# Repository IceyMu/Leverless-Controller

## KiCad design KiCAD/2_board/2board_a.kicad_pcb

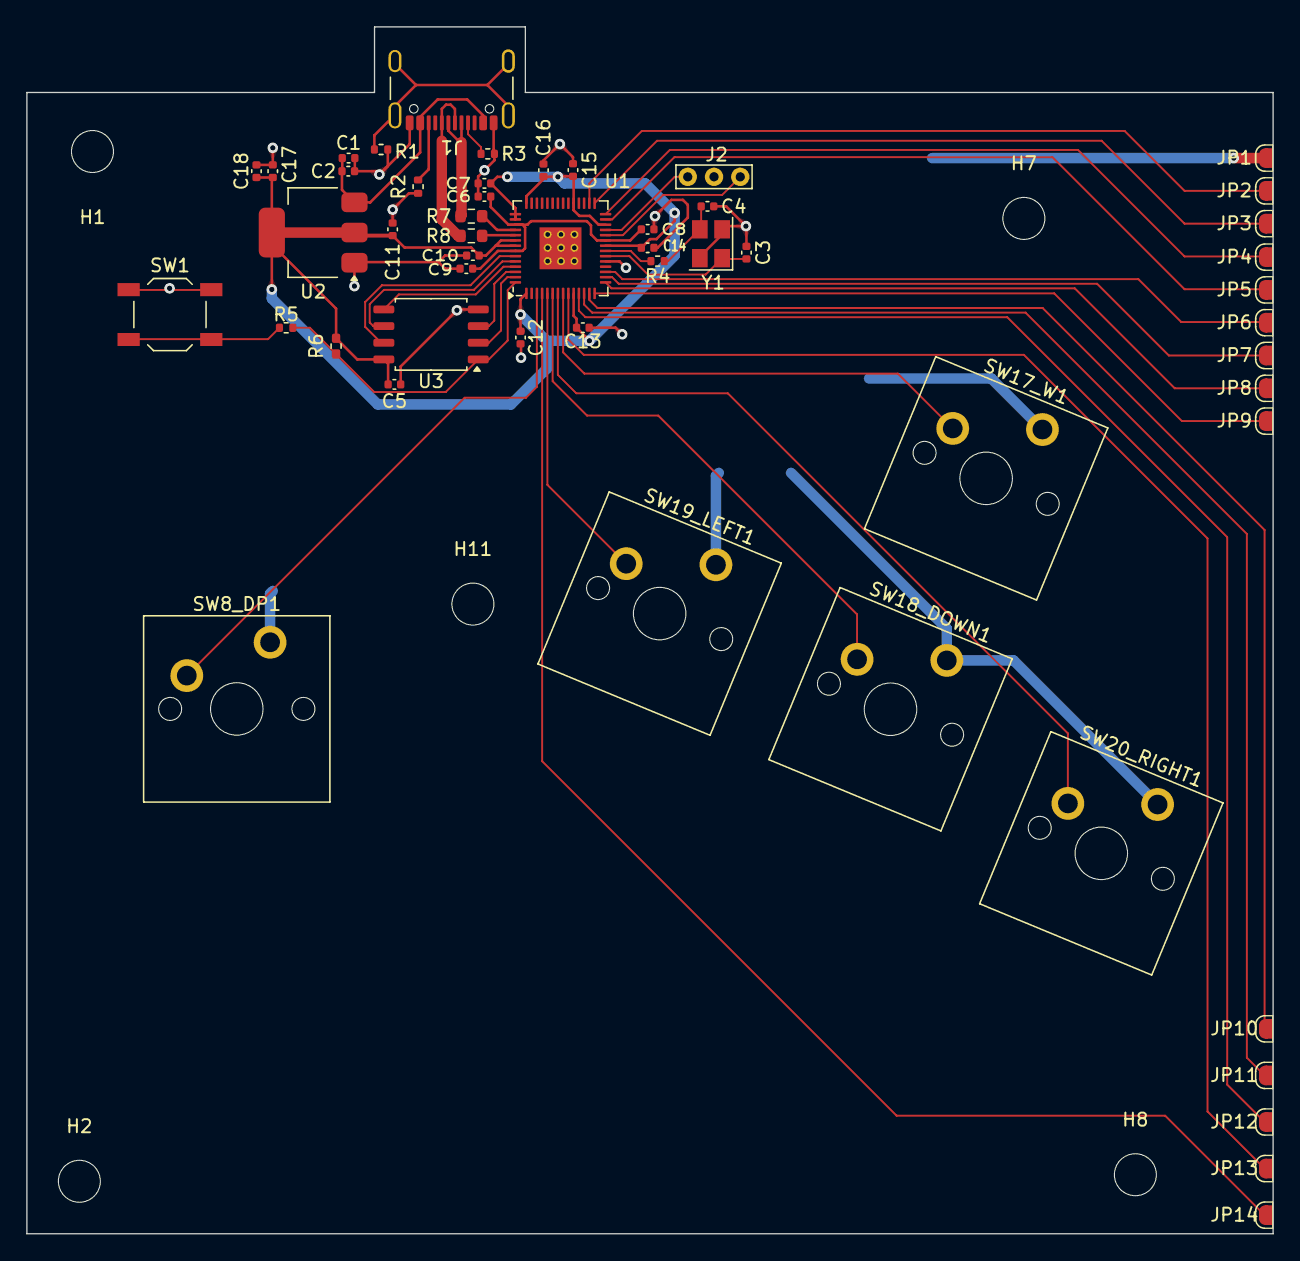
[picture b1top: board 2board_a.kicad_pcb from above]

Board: 2 copper layers, 95.0 x 92.0 mm, 58 parts (0 on the bottom side), 41 nets.

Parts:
B1: Board
C1, C2, C17, C18: 4.7u; C_0402_1005Metric
C3, C4: 15p; C_0402_1005Metric
C5, C8, C9, C10, C11, C12, C13, C14, C15, C16: 100n; C_0402_1005Metric
C6, C7: 1u; C_0402_1005Metric
H1, H2, H7, H8, H11: MountingHole; MountingHole_3.2mm_M3
J1: USB_C_Receptacle_USB2.0_14P; USB_C_Receptacle_U262-161N-4BVC11
J2: Conn_01x03_Socket; Debug_Points
JP1, JP2, JP3, JP4, JP5, JP6, JP7, JP8, JP9, JP10, JP11, JP12, JP13, JP14: SolderJumper_2_Bridged; EdgeSolderJumper-2_Left_Half
R1: 1M; R_0402_1005Metric
R2, R3: 5.1K; R_0402_1005Metric
R4, R5: 1K; R_0402_1005Metric
R6: DNF; R_0402_1005Metric_Pad0.72x0.64mm_HandSolder
R7, R8: 27; R_0603_1608Metric
SW1: Memory Reset; SW_SPST_TL3342
SW8_DP1: SW_Push; SW_Cherry_MX_PCB
SW17_W1, SW18_DOWN1, SW19_LEFT1, SW20_RIGHT1: SW_Push; SW_Cherry_MX_PCB_1.00u
U1: RP2040; QFN-56-1EP_7x7mm_P0.4mm_EP3.2x3.2mm
U2: AMS1117-3.3_SOT223; SOT-223-3_TabPin2
U3: W25Q128JVSIQ; SOIC-8_5.23x5.23mm_P1.27mm
Y1: 12 mhz crystal; Crystal_SMD_3225-4Pin_3.2x2.5mm

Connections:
+1V1: C6.1, C8.1, C9.1, U1.23 (DVDD), U1.45 (VREG_VOUT), U1.50 (DVDD)
+3.3V: C5.1, C7.1, C10.1, C11.1, C12.1, C13.1, C14.1, C15.1, C16.1, C17.1, C18.1, R6.1, U1.1 (IOVDD), U1.10 (IOVDD), U1.22 (IOVDD), U1.26 (RUN), U1.33 (IOVDD), U1.42 (IOVDD), U1.43 (ADC_AVDD), U1.44 (VREG_IN), U1.48 (USB_VDD), U1.49 (IOVDD), U2.2 (VO), U3.8 (VCC)
/Main/A1: JP4.1 (A), U1.28 (GPIO17)
/Main/A2: JP5.1 (A), U1.27 (GPIO16)
/Main/B1: JP13.1 (A), U1.9 (GPIO7)
/Main/B2: JP12.1 (A), U1.11 (GPIO8)
/Main/B3: JP10.1 (A), U1.13 (GPIO10)
/Main/B4: JP8.1 (A), U1.15 (GPIO12)
/Main/D+: J1.A6 (D+), J1.B6 (D+), R8.1
/Main/D-: J1.A7 (D-), J1.B7 (D-), R7.1
/Main/L1: JP6.1 (A), U1.17 (GPIO14)
/Main/L3: JP9.1 (A), U1.14 (GPIO11)
/Main/QSPI_SCLK: U1.52 (QSPI_SCLK), U3.6 (CLK)
/Main/QSPI_SD0: U1.53 (QSPI_SD0), U3.5 (DI(IO0))
/Main/QSPI_SD1: U1.55 (QSPI_SD1), U3.2 (DO(IO1))
/Main/QSPI_SD2: U1.54 (QSPI_SD2), U3.3 (IO2)
/Main/QSPI_SD3: U1.51 (QSPI_SD3), U3.7 (IO3)
/Main/QSPI_SS: R5.2, R6.2, U1.56 (QSPI_SS), U3.1 (~CS)
/Main/R1: JP7.1 (A), U1.16 (GPIO13)
/Main/R2: JP11.1 (A), U1.12 (GPIO9)
/Main/S1: JP3.1 (A), U1.29 (GPIO18)
/Main/S2: JP2.1 (A), U1.30 (GPIO19)
/Main/SPACE: JP14.1 (A), U1.4 (GPIO2)
/Main/SWCLK: J2.1, U1.24 (SWCLK)
/Main/SWDIO: J2.3, U1.25 (SWD)
/Main/XIN: C3.2, U1.20 (XIN), Y1.1
/Main/XOUT: R4.2, U1.21 (XOUT)
DOWN: SW18_DOWN1.1, U1.6 (GPIO4)
GND: C1.2, C2.2, C3.1, C4.1, C5.2, C6.2, C7.2, C8.2, C9.2, C10.2, C11.2, C12.2, C13.2, C14.2, C15.2, C16.2, C17.2, C18.2, J1.A1 (GND), J1.A12 (GND), J1.B1 (GND), J1.B12 (GND), J2.2, JP1.1 (A), R1.2, R2.2, R3.2, SW1.1, SW8_DP1.2, SW17_W1.2, SW18_DOWN1.2, SW19_LEFT1.2, SW20_RIGHT1.2, U1.19 (TESTEN), U1.57 (GND), U2.1 (GND), U3.4 (GND), Y1.2, Y1.4
L2: SW8_DP1.1, U1.3 (GPIO1)
LEFT: SW19_LEFT1.1, U1.5 (GPIO3)
unnamed: C4.2, R4.1, Y1.3
unnamed: J1.A5 (CC1), R3.1
unnamed: J1.B5 (CC2), R2.1
unnamed: J1.S1 (SHIELD), R1.1
unnamed: R5.1, SW1.2
unnamed: R7.2, U1.46 (USB_DM)
unnamed: R8.2, U1.47 (USB_DP)
RIGHT: SW20_RIGHT1.1, U1.7 (GPIO5)
VBUS: C1.1, C2.1, J1.A4 (VBUS), J1.A9 (VBUS), J1.B4 (VBUS), J1.B9 (VBUS), U2.3 (VI)
W: SW17_W1.1, U1.8 (GPIO6)

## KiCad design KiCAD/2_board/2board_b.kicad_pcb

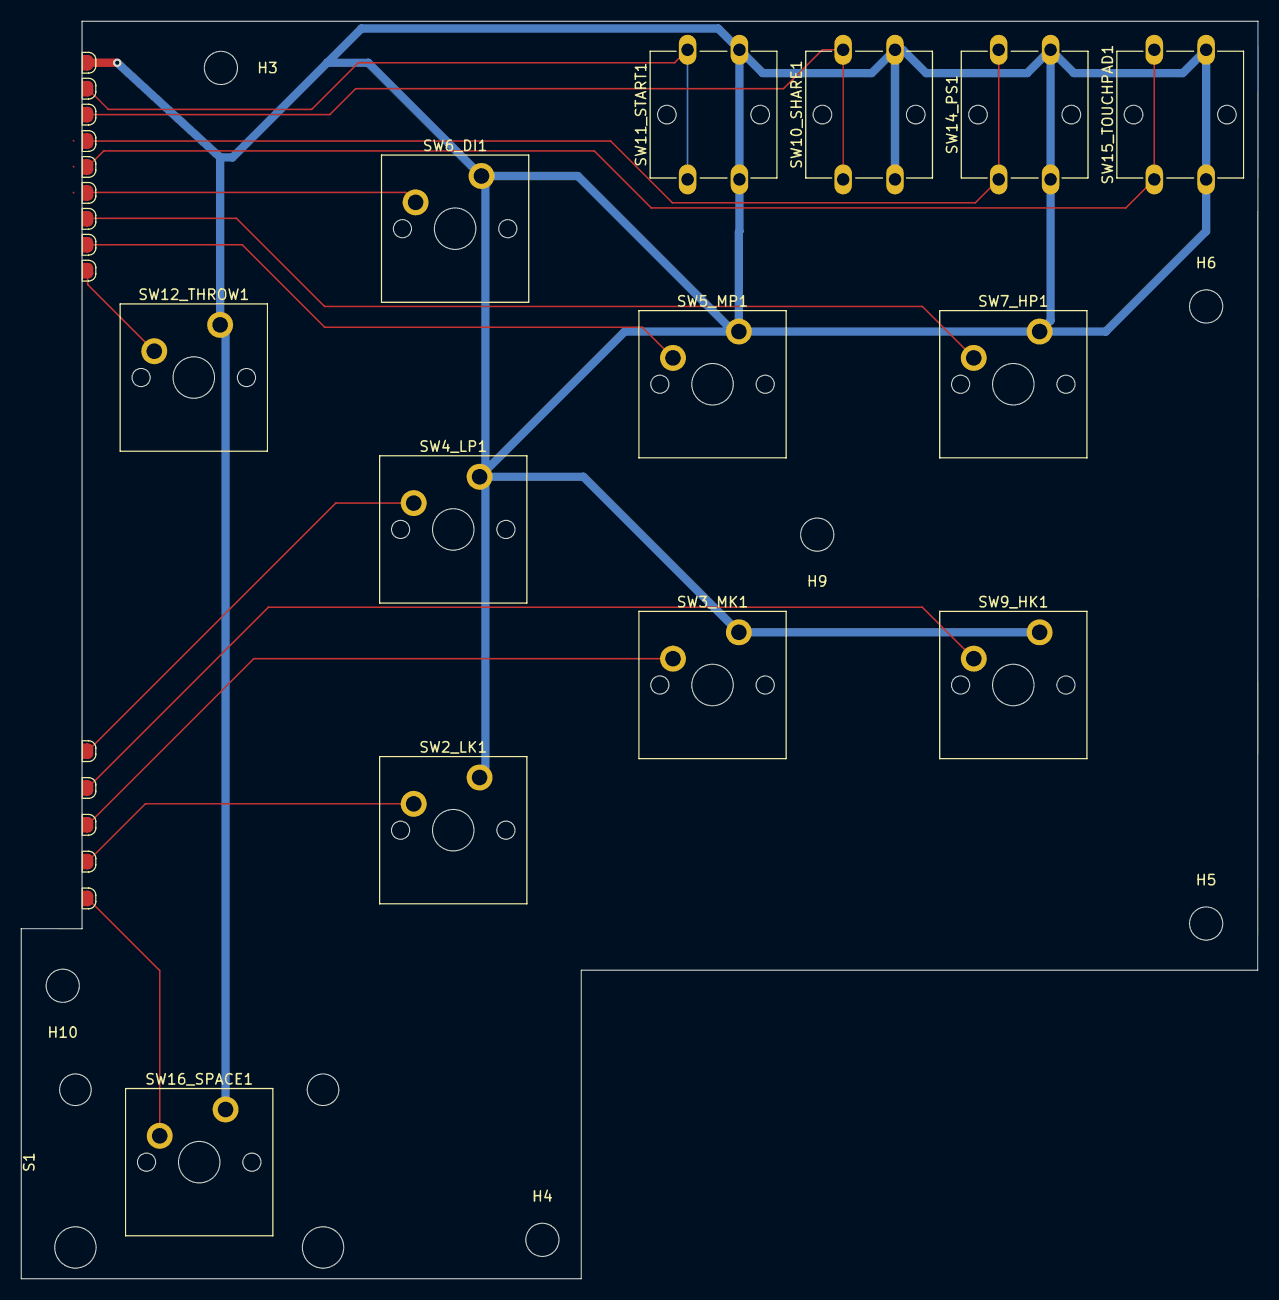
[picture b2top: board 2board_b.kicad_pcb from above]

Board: 2 copper layers, 119.2 x 121.2 mm, 35 parts (0 on the bottom side), 14 nets.

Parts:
B2: Board
H3, H4, H5, H6, H9, H10: MountingHole; MountingHole_3.2mm_M3
JP1, JP2, JP3, JP4, JP5, JP6, JP7, JP8, JP9, JP10, JP11, JP12, JP13, JP14: SolderJumper_2_Bridged; EdgeSolderJumper-2_Right_Half
S1: Stabilizer_Cherry_MX_2.00u
SW2_LK1, SW3_MK1, SW4_LP1, SW5_MP1, SW6_DI1, SW7_HP1, SW9_HK1, SW12_THROW1, SW16_SPACE1: SW_Push; SW_Cherry_MX_PCB
SW10_SHARE1, SW11_START1, SW14_PS1, SW15_TOUCHPAD1: SW_Push; SW_SPST_Omron_B3F-40xx

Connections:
/Buttons/A1: JP4.2 (B), SW14_PS1.1
/Buttons/A2: JP5.2 (B), SW15_TOUCHPAD1.1
/Buttons/B1: JP13.2 (B), SW2_LK1.1
/Buttons/B2: JP12.2 (B), SW3_MK1.1
/Buttons/B3: JP10.2 (B), SW4_LP1.1
/Buttons/B4: JP8.2 (B), SW5_MP1.1
/Buttons/L1: JP6.2 (B), SW6_DI1.1
/Buttons/L3: JP9.2 (B), SW12_THROW1.1
/Buttons/R1: JP7.2 (B), SW7_HP1.1
/Buttons/R2: JP11.2 (B), SW9_HK1.1
/Buttons/S1: JP3.2 (B), SW10_SHARE1.1
/Buttons/S2: JP2.2 (B), SW11_START1.1
/Buttons/SPACE: JP14.2 (B), SW16_SPACE1.1
GND: JP1.2 (B), SW2_LK1.2, SW3_MK1.2, SW4_LP1.2, SW5_MP1.2, SW6_DI1.2, SW7_HP1.2, SW9_HK1.2, SW10_SHARE1.2, SW11_START1.2, SW12_THROW1.2, SW14_PS1.2, SW15_TOUCHPAD1.2, SW16_SPACE1.2

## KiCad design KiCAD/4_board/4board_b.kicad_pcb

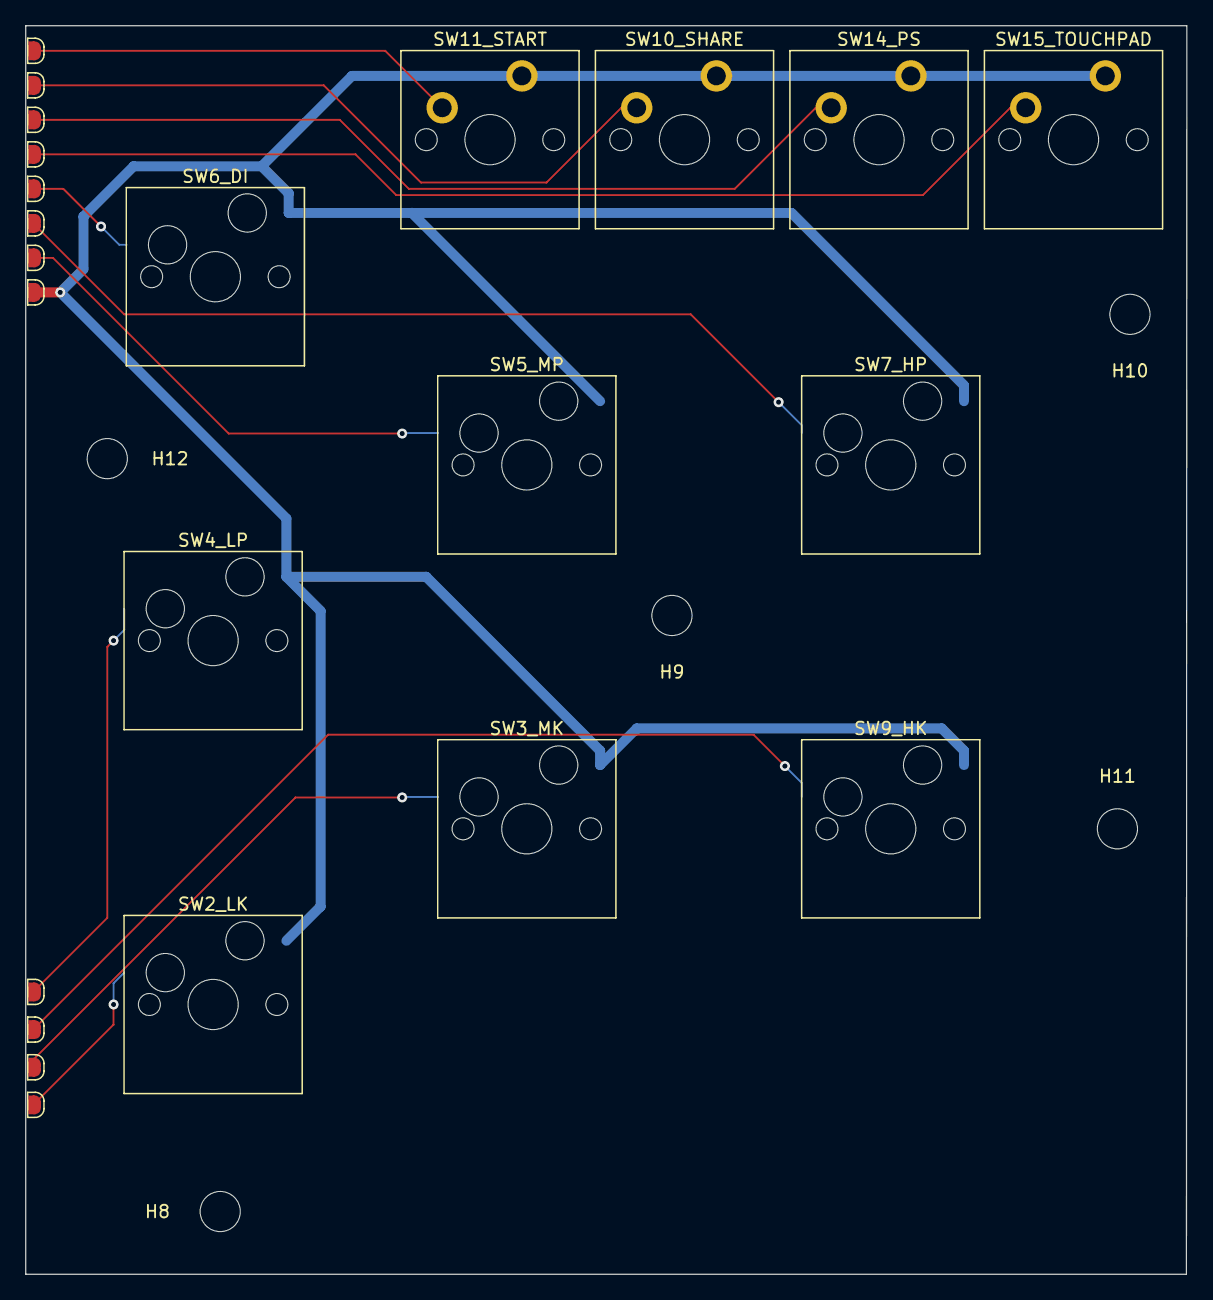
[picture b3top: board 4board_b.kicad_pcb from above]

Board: 2 copper layers, 92.5 x 99.5 mm, 29 parts (0 on the bottom side), 12 nets.

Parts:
B2: Board
H8, H9, H10, H11, H12: MountingHole; MountingHole_3.2mm_M3
JP15, JP17, JP18, JP19, JP20, JP21, JP22, JP23, JP24, JP25, JP26, JP27: SolderJumper_2_Bridged; EdgeSolderJumper-2_Right_Half
SW2_LK, SW3_MK, SW4_LP, SW5_MP, SW6_DI, SW7_HP, SW9_HK: SW_Push; SW_Hotswap_Kailh_MX
SW10_SHARE, SW11_START, SW14_PS, SW15_TOUCHPAD: SW_Push; SW_Cherry_MX_PCB

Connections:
/Buttons/A1: JP23.2 (B), SW14_PS.1
/Buttons/A2: JP24.2 (B), SW15_TOUCHPAD.1
/Buttons/B1: JP20.2 (B), SW2_LK.1
/Buttons/B2: JP19.2 (B), SW3_MK.1
/Buttons/B3: JP17.2 (B), SW4_LP.1
/Buttons/B4: JP27.2 (B), SW5_MP.1
/Buttons/L1: JP25.2 (B), SW6_DI.1
/Buttons/R1: JP26.2 (B), SW7_HP.1
/Buttons/R2: JP18.2 (B), SW9_HK.1
/Buttons/S1: JP22.2 (B), SW10_SHARE.1
/Buttons/S2: JP21.2 (B), SW11_START.1
GND: JP15.2 (B), SW2_LK.2, SW3_MK.2, SW4_LP.2, SW5_MP.2, SW6_DI.2, SW7_HP.2, SW9_HK.2, SW10_SHARE.2, SW11_START.2, SW14_PS.2, SW15_TOUCHPAD.2

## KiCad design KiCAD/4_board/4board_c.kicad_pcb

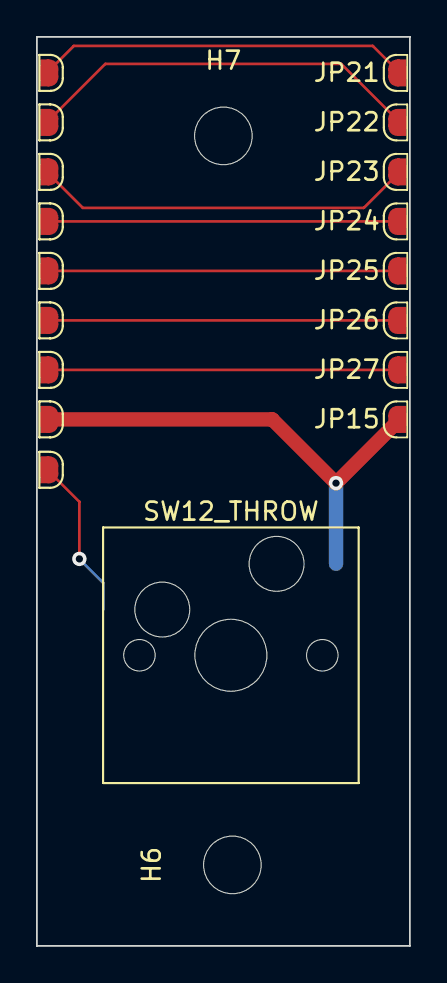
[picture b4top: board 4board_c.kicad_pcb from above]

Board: 2 copper layers, 20.7 x 50.5 mm, 21 parts (0 on the bottom side), 9 nets.

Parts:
B3: Board
H6, H7: MountingHole; MountingHole_3.2mm_M3
JP1, JP2, JP3, JP4, JP5, JP6, JP7, JP8, JP9: SolderJumper_2_Bridged; EdgeSolderJumper-2_Right_Half
JP15, JP21, JP22, JP23, JP24, JP25, JP26, JP27: SolderJumper_2_Bridged; EdgeSolderJumper-2_Left_Half
SW12_THROW: SW_Push; SW_Hotswap_Kailh_MX

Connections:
/Buttons/L3: JP9.2 (B), SW12_THROW.1
GND: JP1.2 (B), JP15.1 (A), SW12_THROW.2
unnamed: JP2.2 (B), JP21.1 (A)
unnamed: JP3.2 (B), JP22.1 (A)
unnamed: JP4.2 (B), JP23.1 (A)
unnamed: JP5.2 (B), JP24.1 (A)
unnamed: JP6.2 (B), JP25.1 (A)
unnamed: JP7.2 (B), JP26.1 (A)
unnamed: JP8.2 (B), JP27.1 (A)

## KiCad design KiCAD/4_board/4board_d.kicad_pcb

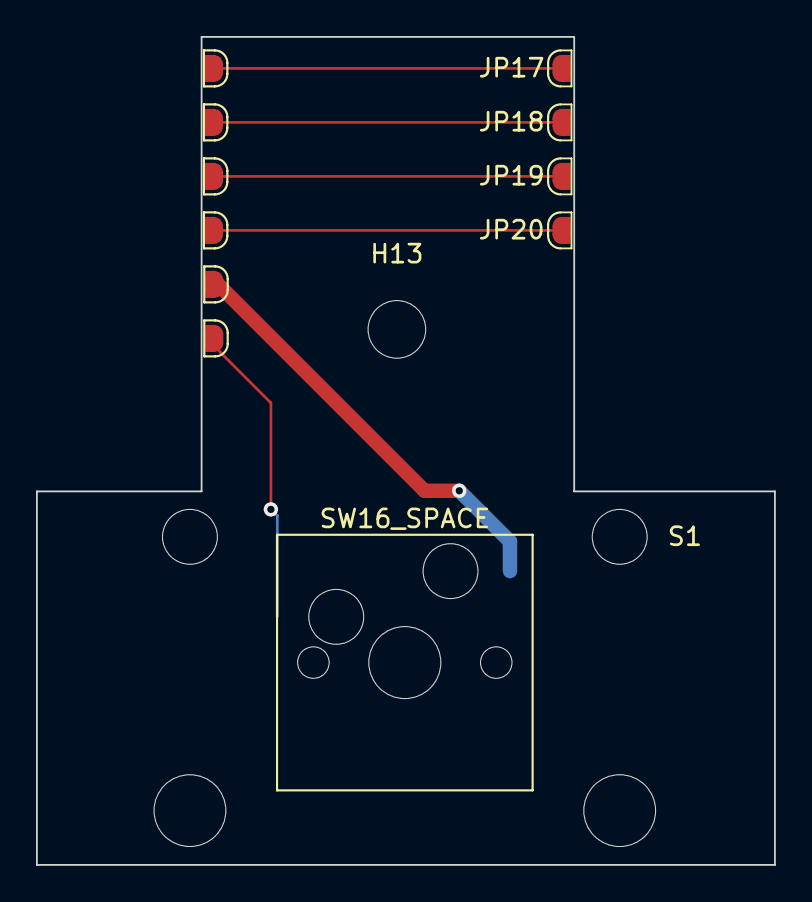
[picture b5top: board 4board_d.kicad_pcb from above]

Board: 2 copper layers, 41.0 x 46.0 mm, 14 parts (0 on the bottom side), 6 nets.

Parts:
B4: Board
H13: MountingHole; MountingHole_3.2mm_M3
JP10, JP11, JP12, JP13, JP14, JP16: SolderJumper_2_Bridged; EdgeSolderJumper-2_Right_Half
JP17, JP18, JP19, JP20: SolderJumper_2_Bridged; EdgeSolderJumper-2_Left_Half
S1: Stabilizer_Cherry_MX_2.00u
SW16_SPACE: SW_Push; SW_Hotswap_Kailh_MX

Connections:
/Buttons/SPACE: JP14.2 (B), SW16_SPACE.1
GND: JP16.2 (B), SW16_SPACE.2
unnamed: JP10.2 (B), JP17.1 (A)
unnamed: JP11.2 (B), JP18.1 (A)
unnamed: JP12.2 (B), JP19.1 (A)
unnamed: JP13.2 (B), JP20.1 (A)
